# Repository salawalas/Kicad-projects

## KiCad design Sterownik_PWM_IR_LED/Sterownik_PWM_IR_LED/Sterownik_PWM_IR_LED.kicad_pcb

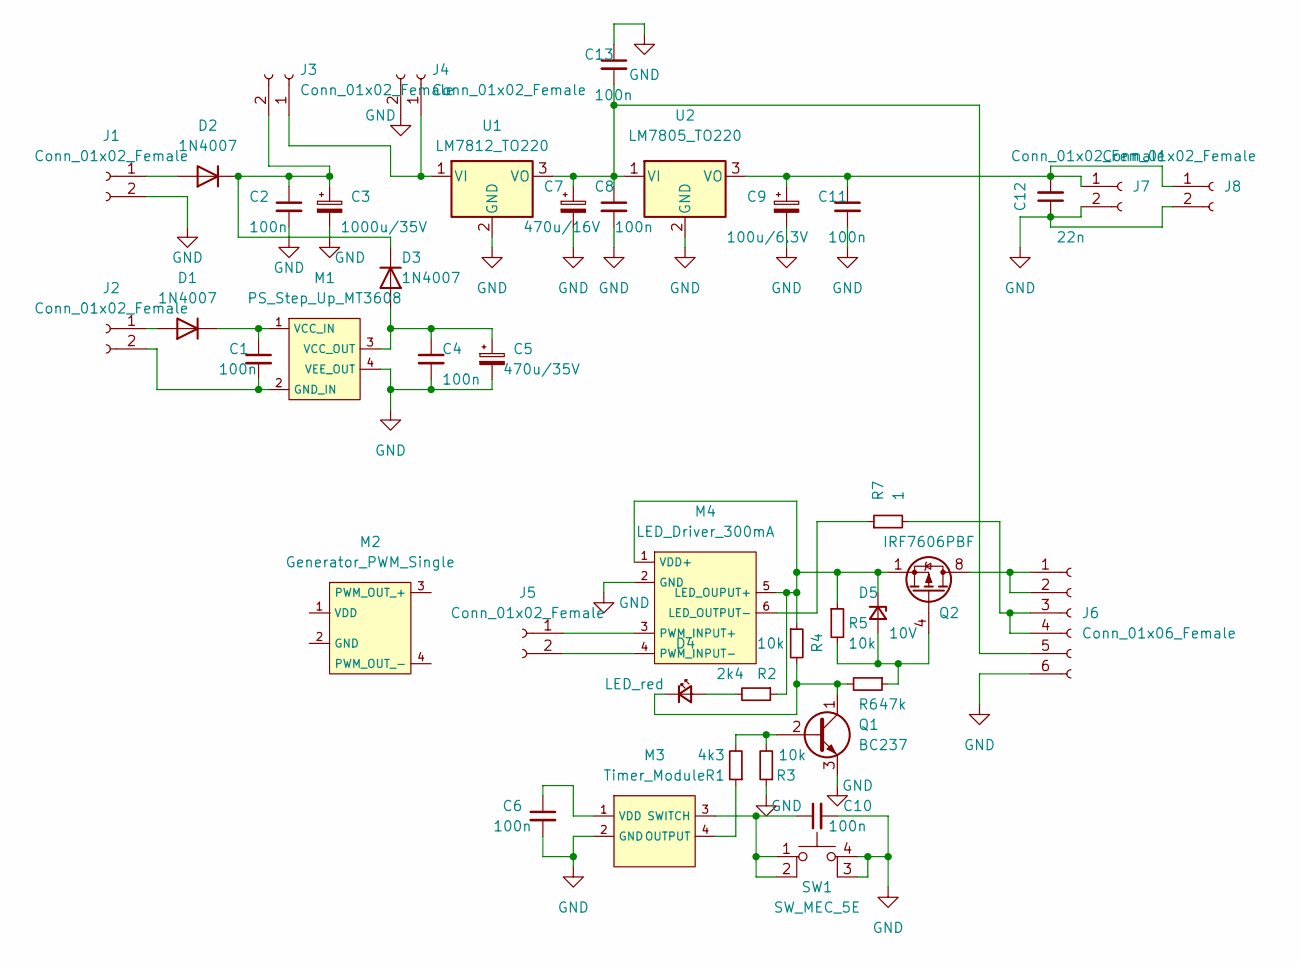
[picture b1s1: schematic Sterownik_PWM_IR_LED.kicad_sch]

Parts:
C1, C2, C4, C8, C11: 100n; C_Rect_L10.0mm_W2.5mm_P7.50mm_MKS4
C3: 1000u/35V; C_Radial_D10.0mm_H20.0mm_P5.00mm
C5: 470u/35V; C_Radial_D10.0mm_H16.0mm_P5.00mm
C6, C10, C13: 100n; C_Disc_D4.7mm_W2.5mm_P5.00mm
C7: 470u/16V; C_Radial_D8.0mm_H11.5mm_P3.50mm
C9: 100u/6.3V; C_Radial_D6.3mm_H7.0mm_P2.50mm
C12: 22n; C_Disc_D4.7mm_W2.5mm_P5.00mm
D1, D2, D3: 1N4007; D_DO-41_SOD81_P10.16mm_Horizontal
D4: LED_red; LED_D3.0mm
D5: 10V; D_DO-34_SOD68_P10.16mm_Horizontal
J1, J2, J3, J4: Conn_01x02_Female; Molex_KK-254_AE-6410-02A_1x02_P2.54mm_Vertical
J5, J7, J8: Conn_01x02_Female; JST_PH_B2B-PH-K_1x02_P2.00mm_Vertical
J6: Conn_01x06_Female; Molex_KK-254_AE-6410-06A_1x06_P2.54mm_Vertical
M1: PS_Step_Up_MT3608; PS_StepUp_MT3608
M2: Generator_PWM_Single
M3: Timer_Module; Timer
M4: LED_Driver_300mA
Q1: BC237; TO-92_Inline
Q2: IRF7606PBF; SO-8_3.9x4.9mm_P1.27mm
R1: 4k3; R_Axial_DIN0207_L6.3mm_D2.5mm_P10.16mm_Horizontal
R2: 2k4; R_Axial_DIN0207_L6.3mm_D2.5mm_P10.16mm_Horizontal
R3, R4, R5: 10k; R_Axial_DIN0207_L6.3mm_D2.5mm_P10.16mm_Horizontal
R6: 47k; R_Axial_DIN0207_L6.3mm_D2.5mm_P10.16mm_Horizontal
R7: 1; R_Axial_DIN0411_L9.9mm_D3.6mm_P12.70mm_Horizontal
SW1: SW_MEC_5E; Tact_switch 6x6
U1: LM7812_TO220; TO-220-3_Horizontal_TabDown
U2: LM7805_TO220; TO-220-3_Vertical

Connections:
unnamed: C1.1, D1.1 (K), M1.1 (VCC_IN)
unnamed: C1.2, J2.2, M1.2 (GND_IN)
unnamed: C4.1, C5.1, D3.2 (A), M1.3 (VCC_OUT)
unnamed: C6.1, M3.1 (VDD)
unnamed: C7.1, C8.1, C13.2, J6.5, U1.3 (VO), U2.1 (VI)
unnamed: C10.1, M3.3 (SWITCH), SW1.1, SW1.2
unnamed: C9.1, C11.1, C12.2, J7.1, J8.1, U2.3 (VO)
unnamed: D1.2 (A), J2.1
unnamed: D2.2 (A), J1.1
unnamed: D4.1 (K), Q1.1 (C), R4.2, R6.2
unnamed: D4.2 (A), R2.2
unnamed: D5.1 (K), M4.1 (VDD+), M4.5 (LED_OUPUT+), Q2.1 (S), Q2.2 (S), Q2.3 (S), R2.1, R4.1, R5.1
unnamed: D5.2 (A), Q2.4 (G), R5.2, R6.1
unnamed: J3.1, J4.1, U1.1 (VI)
unnamed: J5.1, M4.3 (PWM_INPUT+)
unnamed: J5.2, M4.4 (PWM_INPUT-)
unnamed: J6.1, J6.2, Q2.5 (D), Q2.6 (D), Q2.7 (D), Q2.8 (D)
unnamed: J6.3, J6.4, R7.2
unnamed: M3.4 (OUTPUT), R1.1
unnamed: M4.6 (LED_OUTPUT-), R7.1
unnamed: Q1.2 (B), R1.2, R3.2

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
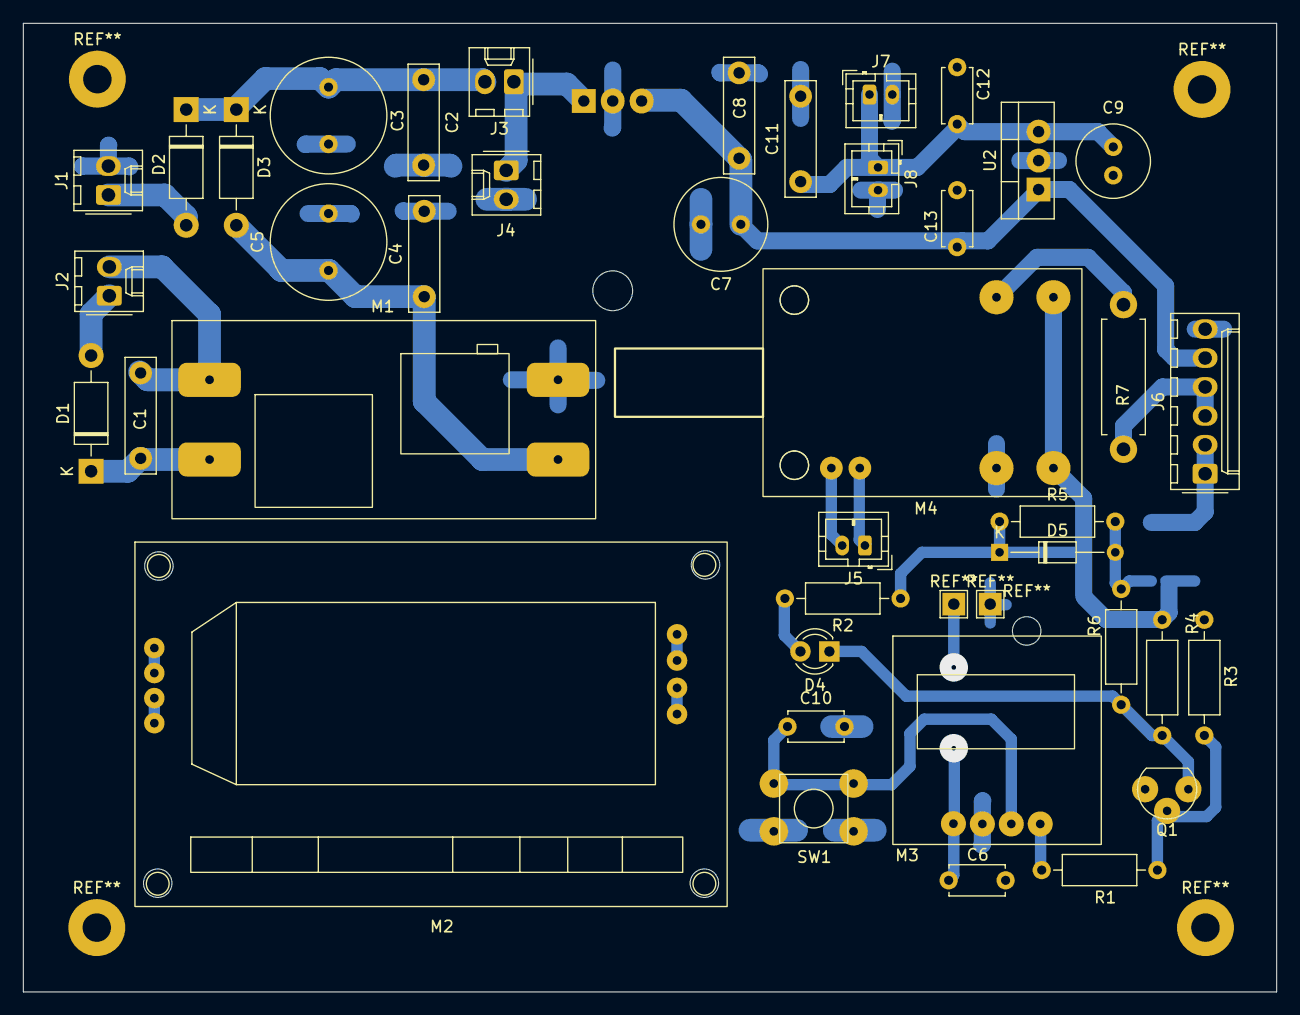
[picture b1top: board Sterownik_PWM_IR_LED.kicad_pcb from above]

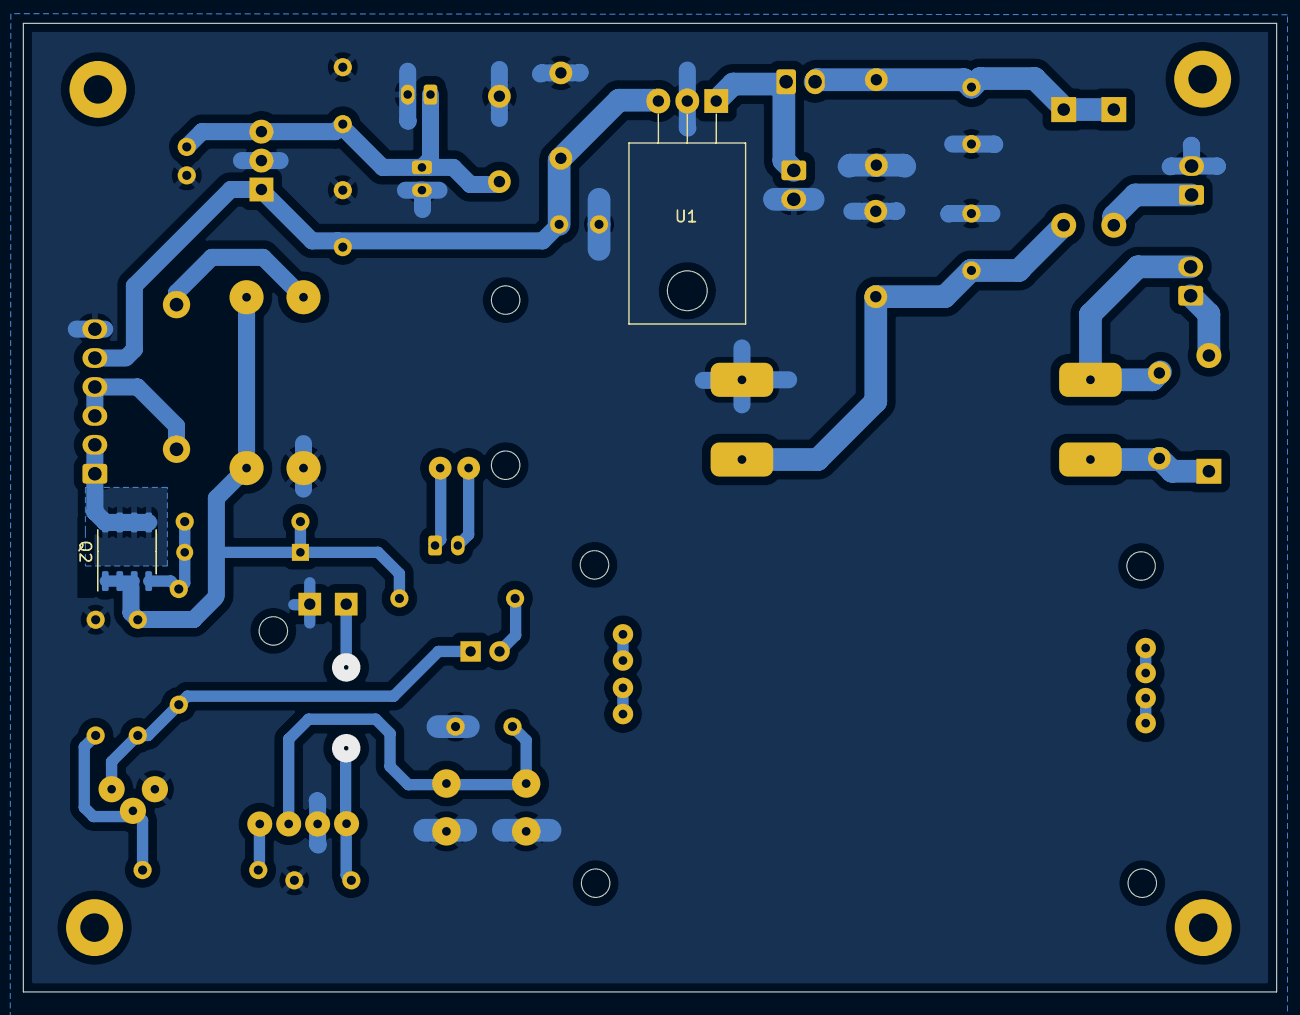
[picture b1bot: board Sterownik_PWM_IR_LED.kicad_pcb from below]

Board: 2 copper layers, 110.0 x 85.1 mm, 42 parts (2 on the bottom side), 23 nets.

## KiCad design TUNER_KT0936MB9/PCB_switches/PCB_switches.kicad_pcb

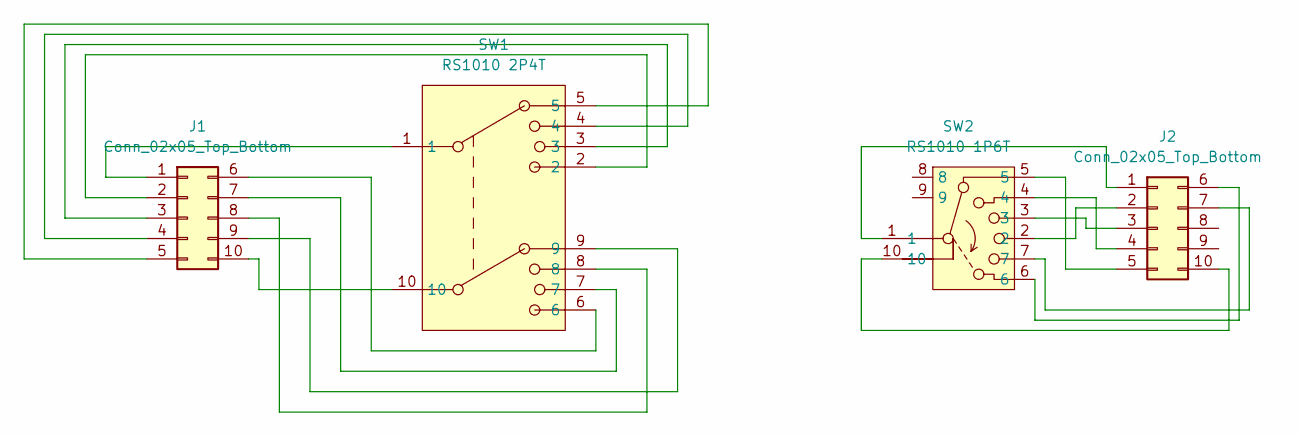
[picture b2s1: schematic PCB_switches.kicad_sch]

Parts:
J1, J2: Conn_02x05_Top_Bottom; JST_PHD_B10B-PHDSS_2x05_P2.00mm_Vertical
SW1: RS1010 2P4T
SW2: RS1010 1P6T

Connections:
unnamed: J1.1, SW1.1
unnamed: J1.2, SW1.2
unnamed: J1.3, SW1.3
unnamed: J1.4, SW1.4
unnamed: J1.5, SW1.5
unnamed: J1.6, SW1.6
unnamed: J1.7, SW1.7
unnamed: J1.8, SW1.8
unnamed: J1.9, SW1.9
unnamed: J1.10, SW1.10
unnamed: J2.1, SW2.1
unnamed: J2.2, SW2.2
unnamed: J2.3, SW2.3
unnamed: J2.4, SW2.4
unnamed: J2.5, SW2.5
unnamed: J2.6, SW2.6
unnamed: J2.7, SW2.7
unnamed: J2.10, SW2.10

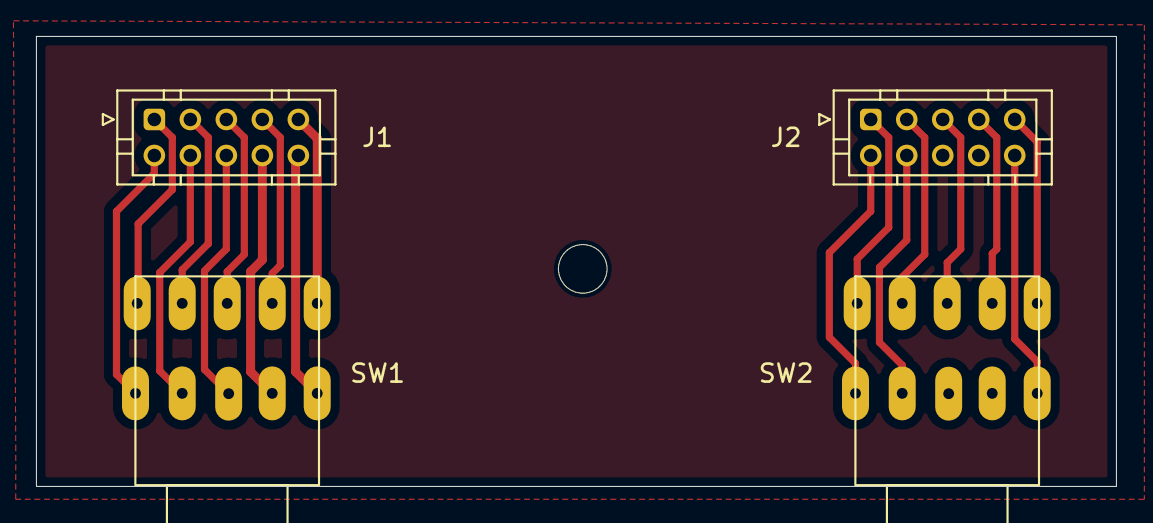
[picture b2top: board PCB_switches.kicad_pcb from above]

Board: 2 copper layers, 60.0 x 25.0 mm, 4 parts (0 on the bottom side), 18 nets.

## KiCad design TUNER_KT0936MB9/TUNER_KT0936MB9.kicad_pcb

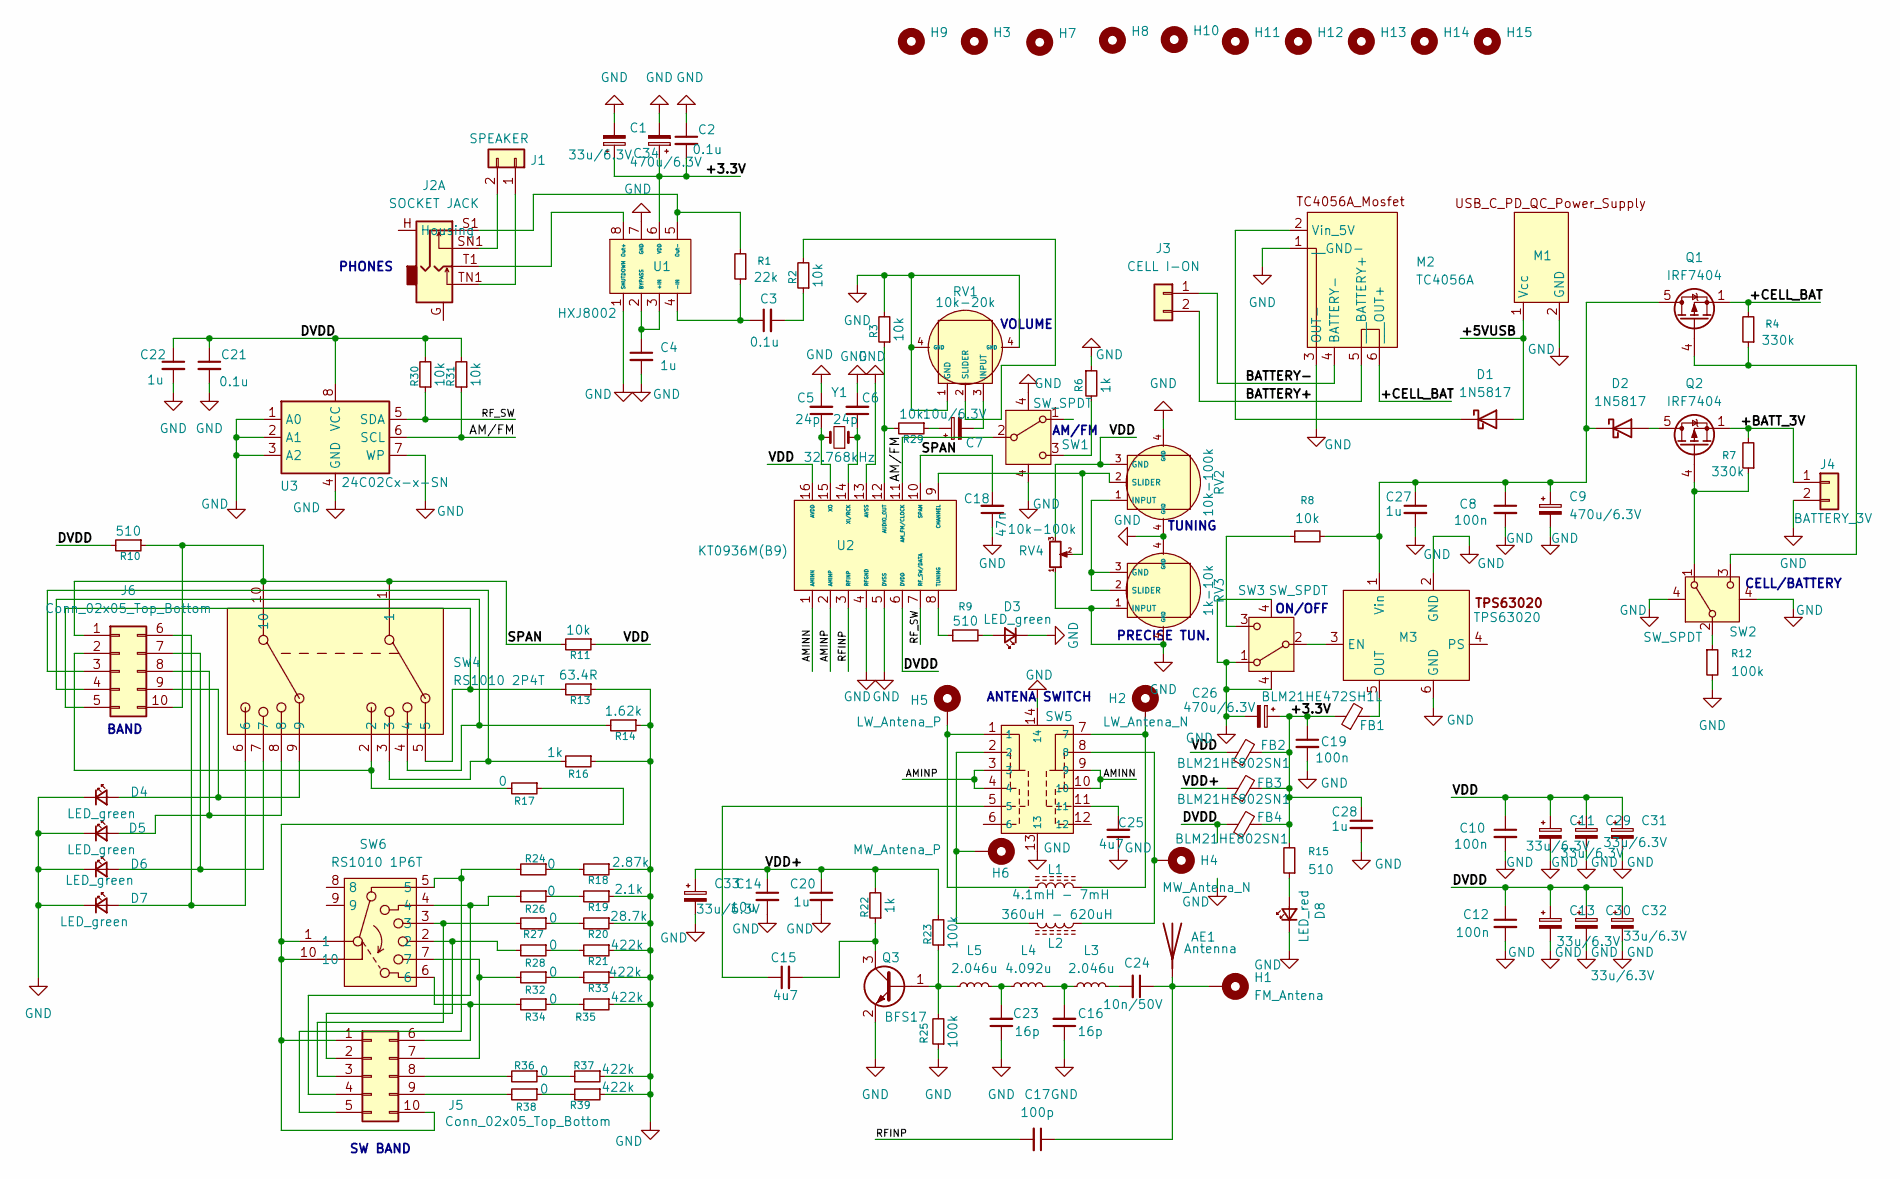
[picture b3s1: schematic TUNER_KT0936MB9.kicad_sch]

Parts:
AE1: Antenna
C1: 470u/6.3V; CP_Radial_D8.0mm_P3.80mm
C2, C3, C21: 0.1u; C_1206_3216Metric
C4, C20, C22, C27, C28: 1u; C_1206_3216Metric
C5, C6: 24p; C_0805_2012Metric
C7: 10u/6.3V; CP_Radial_D5.0mm_P2.50mm
C8, C10, C12, C19: 100n; C_1206_3216Metric
C9, C26: 470u/6.3V; CP_Radial_D8.0mm_P3.50mm
C11, C13, C29, C30, C31, C32, C33, C34: 33u/6.3V; CP_Radial_Tantal_D4.5mm_P2.50mm
C14: 10u; C_1206_3216Metric
C15, C25: 4u7; C_1206_3216Metric
C16, C23: 16p; C_0805_2012Metric
C17: 100p; C_0805_2012Metric
C18: 47n; C_0805_2012Metric
C24: 10n/50V; C_0805_2012Metric
D1, D2: 1N5817; D_DO-41_SOD81_P10.16mm_Horizontal
D3, D4, D5, D6, D7: LED_green; LED_D3.0mm
D8: LED_red; LED_D3.0mm
FB1: BLM21HE472SH1L; L_0805_2012Metric
FB2, FB3, FB4: BLM21HE802SN1; L_0805_2012Metric
H1: FM_Antena; SolderWire-0.1sqmm_1x01_D0.4mm_OD1mm
H2: LW_Antena_N; SolderWire-0.1sqmm_1x01_D0.4mm_OD1mm
H3, H7, H8, H9, H10, H11, H12, H13, H14, H15: MountingHole; MountingHole_2.2mm_M2
H4: MW_Antena_N; SolderWire-0.1sqmm_1x01_D0.4mm_OD1mm
H5: LW_Antena_P; SolderWire-0.1sqmm_1x01_D0.4mm_OD1mm
H6: MW_Antena_P; SolderWire-0.1sqmm_1x01_D0.4mm_OD1mm
J1: SPEAKER; JST_EH_B2B-EH-A_1x02_P2.50mm_Vertical
J2: SOCKET JACK; Jack_3.5mm_PJ31060-I_Horizontal
J3: CELL I-ON; JST_EH_B2B-EH-A_1x02_P2.50mm_Vertical
J4: BATTERY_3V; JST_EH_B2B-EH-A_1x02_P2.50mm_Vertical
J5, J6: Conn_02x05_Top_Bottom; JST_PHD_B10B-PHDSS_2x05_P2.00mm_Vertical
L1: 4.1mH - 7mH
L2: 360uH - 620uH
L3, L5: 2.046u; Cewka_5mm_LITZA
L4: 4.092u; Cewka_5mm_LITZA
M1: USB_C_PD_QC_Power_SupplyUSB_C_PS
M2: TC4056A; TC4056A_Mosfet
M3: TPS63020; TPS63020_module
Q1, Q2: IRF7404; SOIC-8_3.9x4.9mm_P1.27mm
Q3: BFS17; SOT-23
R1: 22k; R_1206_3216Metric
R2, R3, R11, R29, R30, R31: 10k; R_0805_2012Metric
R4, R7: 330k; R_1206_3216Metric
R6, R22: 1k; R_0805_2012Metric
R8: 10k; R_1206_3216Metric
R9, R10, R15: 510; R_1206_3216Metric
R12: 100k; R_1206_3216Metric
R13: 63.4R; R_1206_3216Metric
R14: 1.62k; R_1206_3216Metric
R16: 1k; R_1206_3216Metric
R17, R24, R26, R27, R28, R32, R34, R36, R38: 0; R_1206_3216Metric
R18: 2.87k; R_1206_3216Metric
R19: 2.1k; R_1206_3216Metric
R20: 28.7k; R_1206_3216Metric
R21, R33, R35, R37, R39: 422k; R_1206_3216Metric
R23, R25: 100k; R_0805_2012Metric
RV1: 10k-20k; Potencjometr_pojedynczy_thumbweel.mp3
RV2: 10k-100k; Potencjometr_pojedynczy_thumbweel.mp3
RV3: 1k-10k; Potencjometr_pojedynczy_thumbweel.mp3
RV4: 10k-100k; Potentiometer_Bourns_3296W_Vertical
SW1: SW_SPDT; SS-12F44G5
SW2, SW3: SW_SPDT; SK-12D07VG5
SW4: RS1010 2P4T
SW5: SK-24D02-G4
SW6: RS1010 1P6T
U1: HXJ8002; SOP-8_3.76x4.96mm_P1.27mm
U2: KT0936M(B9); SOP-16_3.9x9.9mm_P1.27mm
U3: 24C02Cx-x-SN; SOIC-8_3.9x4.9mm_P1.27mm
Y1: 32.768kHz; Crystal_AT310_D3.0mm_L10.0mm_Horizontal

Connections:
/+3.3V: C1.1, C2.2, C19.1, C26.1, C28.1, C34.1, FB1.1, FB2.2, FB3.2, FB4.2, R15.2, U1.6 (VDD)
/+5VUSB: D1.2 (A), M1.1 (Vcc)
/+BATT_3V: J4.1, Q2.1 (S), Q2.2 (S), Q2.3 (S), R7.2
/+CELL_BAT: M2.6 (___OUT+), Q1.1 (S), Q1.2 (S), Q1.3 (S), R4.2
/AMINN: SW5.9, SW5.10, U2.1 (AMINN)
/AMINP: SW5.3, SW5.4, U2.2 (AMINP)
/AM/FM: R31.1, SW1.2 (B), U2.11 (AM_FM/CLOCK), U3.6 (SCL)
/BATTERY+: J3.2, M2.5 (___BATTERY+)
/BATTERY-: J3.1, M2.4 (BATTERY-)
/DVDD: C12.1, C13.1, C21.1, C22.1, C30.1, C32.1, FB4.1, R10.2, R30.2, R31.2, U2.6 (DVDD), U3.8 (VCC)
/RFINP: C17.2, U2.3 (RFINP)
/RF_SW: R30.1, U2.7 (RF_SW/DATA), U3.5 (SDA)
/SPAN: C18.2, J6.1, J6.10, R10.1, R11.2, SW4.1, SW4.10, U2.10 (SPAN)
/VDD: C10.1, C11.1, C29.1, C31.1, FB2.1, R11.1, RV2.3 (GND), RV4.3, U2.16 (AVDD)
/VDD+: C14.1, C20.1, C33.1, FB3.1, R22.2, R23.2
GND: C1.2, C2.1, C4.2, C5.2, C6.2, C8.2, C9.2, C10.2, C11.2, C12.2, C13.2, C14.2, C16.1, C18.1, C19.2, C20.2, C21.2, C22.2, C23.1, C25.1, C26.2, C27.2, C28.2, C29.2, C30.2, C31.2, C32.2, C33.2, C34.2, D3.1 (K), D4.1 (K), D5.1 (K), D6.1 (K), D7.1 (K), D8.1 (K), J4.2, M1.2 (GND), M2.1 (__GND-), M2.3 (OUT-), M3.2 (GND), M3.6 (GND), Q3.2 (E), R3.2, R6.1, R12.2, R13.1, R14.1, R16.1, R18.1, R19.1, R20.1, R21.1, R25.1, R33.1, R35.1, R37.1, R39.1, RV1.1 (GND), RV1.4 (GND), RV2.4 (GND), RV3.1 (INPUT), RV3.4 (GND), RV4.1, SW1.4, SW2.4, SW3.1 (A), SW3.4, SW5.13, SW5.14, U1.1 (SHUTDOWN), U1.7 (GND), U2.4 (RFGND), U2.5 (DVSS), U2.13 (AVSS), U3.1 (A0), U3.2 (A1), U3.3 (A2), U3.4 (GND), U3.7 (WP)
unnamed: C3.2, R2.1
unnamed: C7.1, R29.1
unnamed: C15.1, SW5.5
unnamed: C16.2, L3.1, L4.2
unnamed: AE1.1, C17.1, C24.1, H1.1
unnamed: C23.2, L4.1, L5.2
unnamed: C24.2, L3.2
unnamed: C25.2, SW5.11
unnamed: D1.1 (K), M2.2 (Vin_5V)
unnamed: D2.2 (A), Q2.5 (D), Q2.6 (D), Q2.7 (D), Q2.8 (D)
unnamed: C8.1, C9.1, C27.1, D2.1 (K), M3.1 (Vin), Q1.5 (D), Q1.6 (D), Q1.7 (D), Q1.8 (D), R8.2
unnamed: D3.2 (A), R9.2
unnamed: D4.2 (A), J6.9, SW4.9
unnamed: D5.2 (A), J6.8, SW4.8
unnamed: D6.2 (A), J6.7, SW4.7
unnamed: D7.2 (A), J6.6, SW4.6
unnamed: D8.2 (A), R15.1
unnamed: H2.1, L1.2, SW5.7
unnamed: H4.1, L2.1, SW5.8
unnamed: H5.1, L1.1, SW5.1
unnamed: H6.1, L2.2, SW5.2
unnamed: J1.1, J2.TN1
unnamed: J1.2, J2.SN1
unnamed: J5.1, J5.10, R17.1, SW6.1, SW6.10
unnamed: J5.2, R28.2, SW6.2
unnamed: J5.3, R27.2, SW6.3
unnamed: J5.4, R26.2, SW6.4
unnamed: J5.5, R24.2, SW6.5
unnamed: J5.6, R34.2, SW6.6
unnamed: J5.7, R32.2, SW6.7
unnamed: J5.8, R36.2
unnamed: J5.9, R38.2
unnamed: J6.2, R17.2, SW4.2
unnamed: J6.3, R16.2, SW4.3
unnamed: J6.4, R14.2, SW4.4
unnamed: J6.5, R13.2, SW4.5
unnamed: M3.3 (EN), SW3.2 (B)
unnamed: FB1.2, M3.5 (OUT)
unnamed: Q1.4 (G), R4.1, SW2.3 (C)
unnamed: Q2.4 (G), R7.1, SW2.1 (A)
unnamed: L5.1, Q3.1 (B), R23.1, R25.2
unnamed: C15.2, Q3.3 (C), R22.1
unnamed: R18.2, R24.1
unnamed: R19.2, R26.1
unnamed: R20.2, R27.1
unnamed: R21.2, R28.1
unnamed: R32.1, R33.2
unnamed: R34.1, R35.2
unnamed: R36.1, R37.2
unnamed: R38.1, R39.2
unnamed: C7.2, RV1.3 (INPUT)
unnamed: R2.2, RV1.2 (SLIDER)
unnamed: RV2.1 (INPUT), RV3.2 (SLIDER), RV3.3 (GND)
unnamed: RV2.2 (SLIDER), RV4.2, U2.9 (CHANNEL)
unnamed: R6.2, SW1.3 (C)
unnamed: R12.1, SW2.2 (B)
unnamed: R8.1, SW3.3 (C)
unnamed: C4.1, U1.2 (BYPASS), U1.3 (+IN)
unnamed: C3.1, R1.1, U1.4 (-IN)
unnamed: J2.T1, U1.8 (Out+)
unnamed: J2.S1, R1.2, U1.5 (Out-)
unnamed: R3.1, R29.2, U2.12 (AUDIO_OUT)
unnamed: R9.1, U2.8 (TUNING)
unnamed: C6.1, U2.14 (XI/RCK), Y1.1
unnamed: C5.1, U2.15 (XO), Y1.2

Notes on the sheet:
ANTENA SWITCH
TUNING
PHONES
ON/OFF
VOLUME
AM/FM
CELL/BATTERY
BAND
PRECISE TUN.
SW BAND

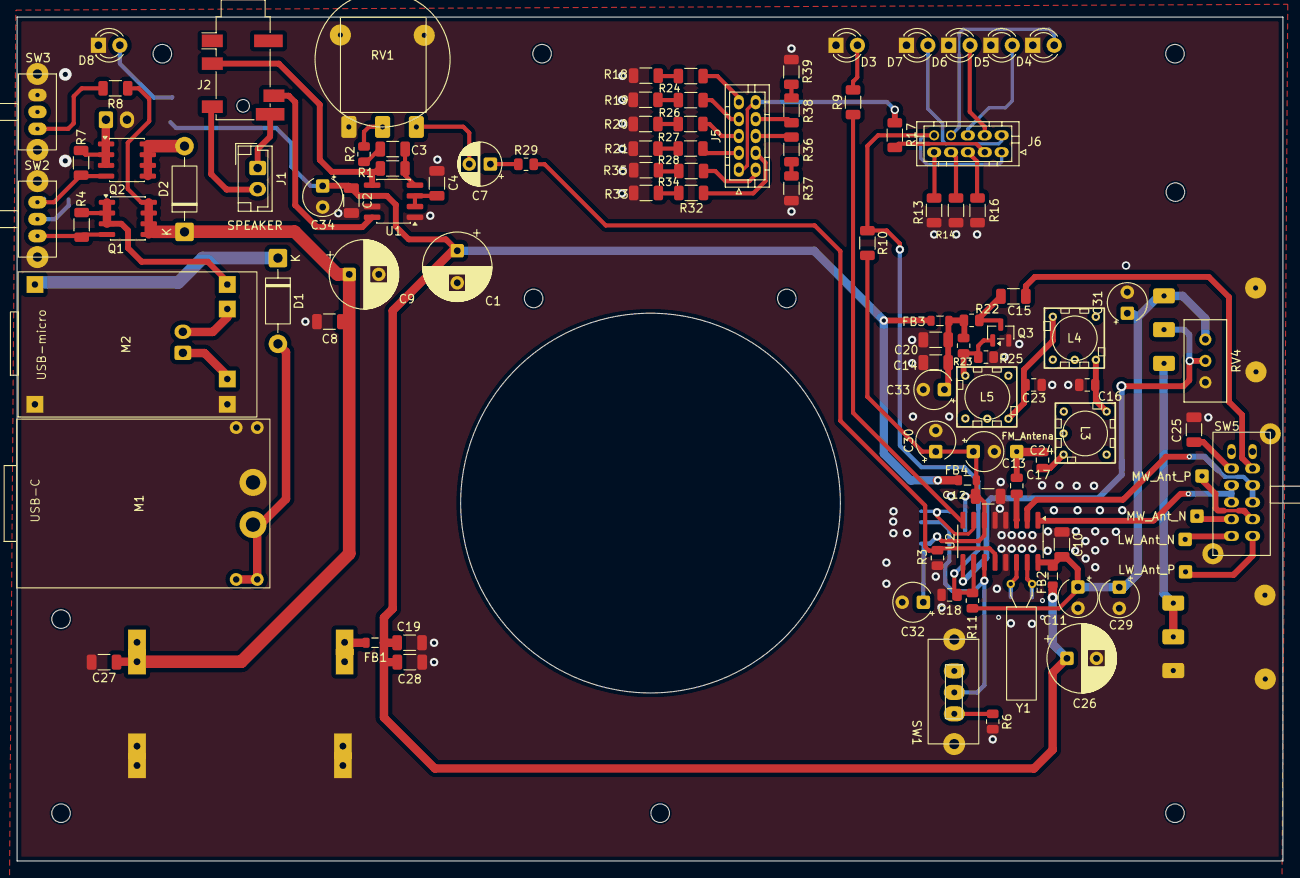
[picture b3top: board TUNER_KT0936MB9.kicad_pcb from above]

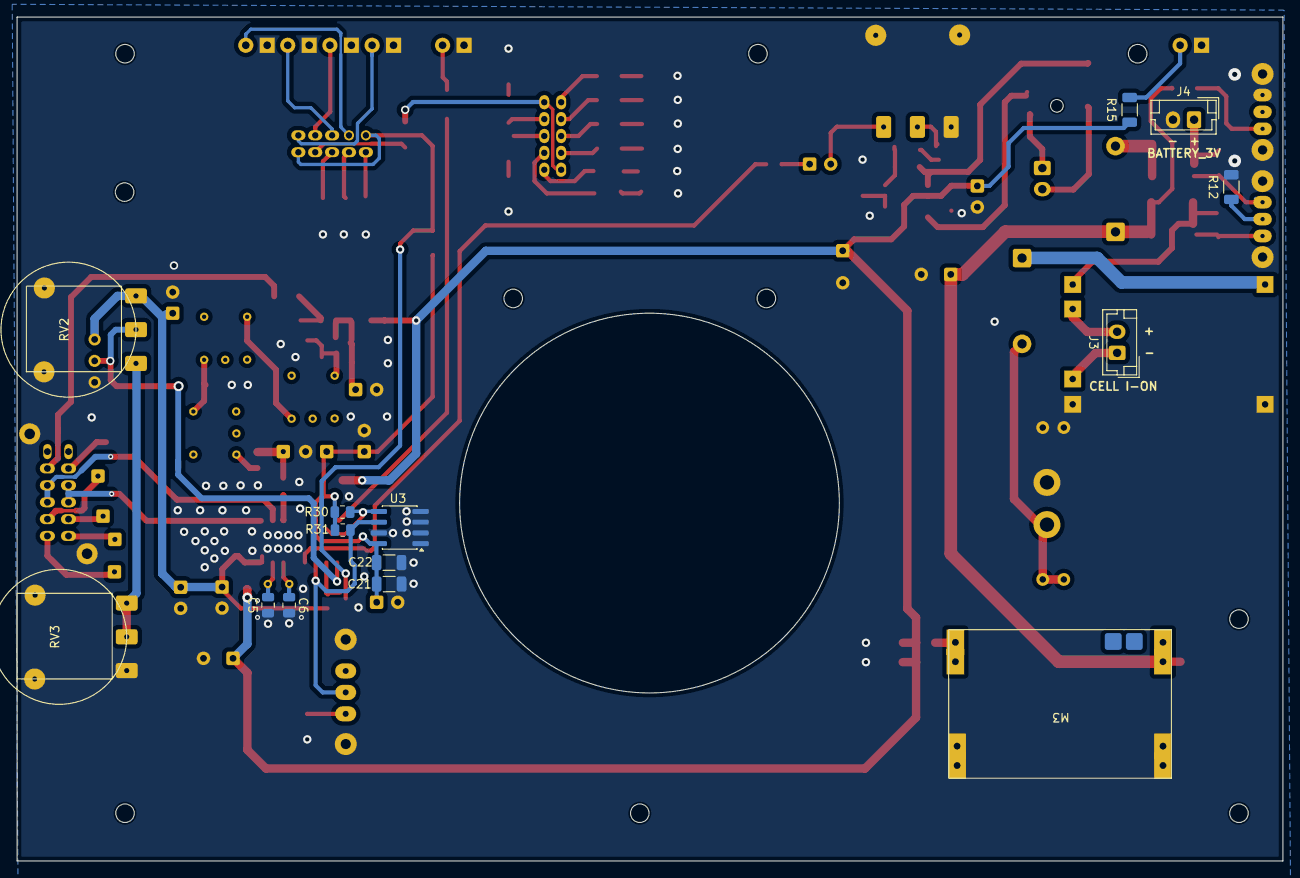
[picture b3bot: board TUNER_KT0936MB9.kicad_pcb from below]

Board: 2 copper layers, 150.0 x 100.0 mm, 126 parts (14 on the bottom side), 81 nets.

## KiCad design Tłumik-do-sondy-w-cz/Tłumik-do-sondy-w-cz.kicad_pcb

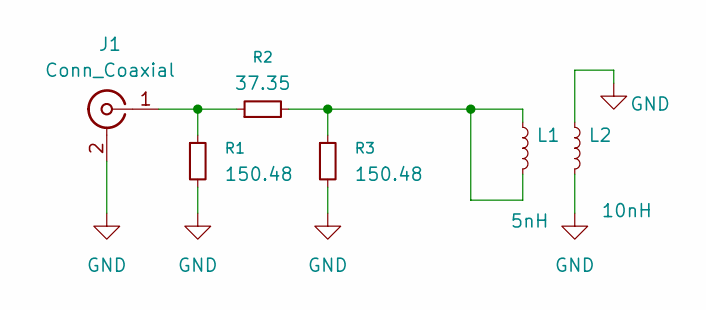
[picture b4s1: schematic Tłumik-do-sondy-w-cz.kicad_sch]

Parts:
J1: Conn_Coaxial; SMA_Molex_73251-1153_EdgeMount_Horizontal
L1: 5nH; L_Radial_D6.0mm_P4.00mm
L2: 10nH; L_Radial_D12.0mm_P10.00mm_Neosid_SD12k_style1
R1, R3: 150.48; R_0805_2012Metric
R2: 37.35; R_0805_2012Metric

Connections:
GND: J1.2 (Ext), L2.1, L2.2, R1.2, R3.2
unnamed: J1.1 (In), R1.1, R2.1
unnamed: L1.1, L1.2, R2.2, R3.1

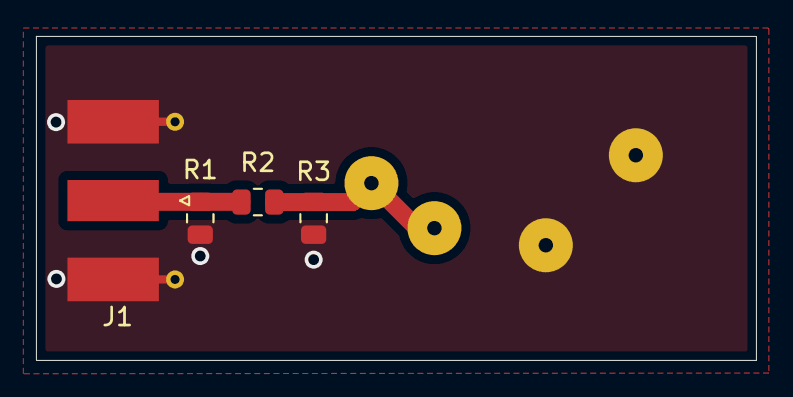
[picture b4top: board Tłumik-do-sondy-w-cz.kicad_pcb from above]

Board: 4 copper layers, 40.0 x 18.0 mm, 6 parts (0 on the bottom side), 3 nets.

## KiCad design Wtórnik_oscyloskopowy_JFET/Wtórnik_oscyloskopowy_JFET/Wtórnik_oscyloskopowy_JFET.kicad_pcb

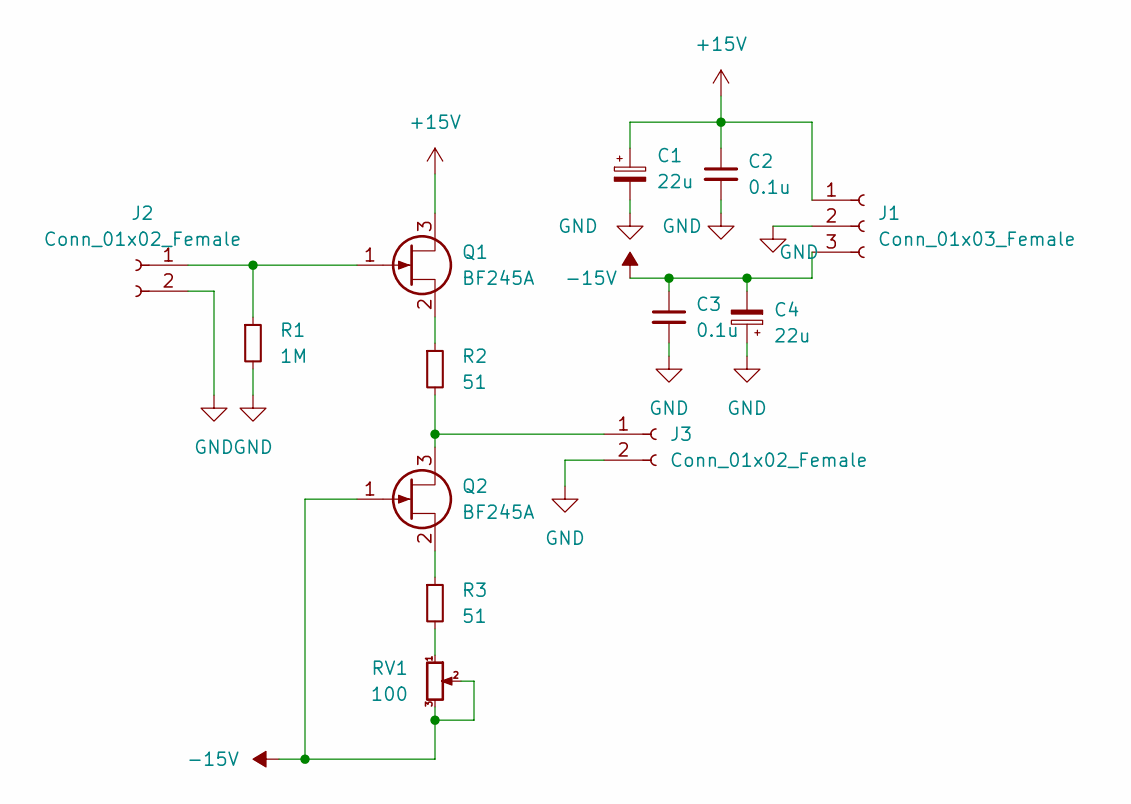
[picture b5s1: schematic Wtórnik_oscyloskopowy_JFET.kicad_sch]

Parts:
C1, C4: 22u; CP_Radial_Tantal_D5.0mm_P5.00mm
C2, C3: 0.1u; C_0805_2012Metric
J1: Conn_01x03_Female; PinHeader_1x03_P2.54mm_Vertical
J2, J3: Conn_01x02_Female; PinHeader_1x02_P2.54mm_Vertical
Q1, Q2: BF245A; TO-92
R1: 1M; R_0805_2012Metric
R2, R3: 51; R_0805_2012Metric
RV1: 100; Potentiometer_Bourns_3266Y_Vertical

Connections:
+15V: C1.1, C2.1, J1.1, Q1.3 (D)
-15V: C3.1, C4.2, J1.3, Q2.1 (G), RV1.2, RV1.3
GND: C1.2, C2.2, C3.2, C4.1, J1.2, J2.2, J3.2, R1.2
unnamed: J2.1, Q1.1 (G), R1.1
unnamed: J3.1, Q2.3 (D), R2.2
unnamed: Q1.2 (S), R2.1
unnamed: Q2.2 (S), R3.1
unnamed: R3.2, RV1.1

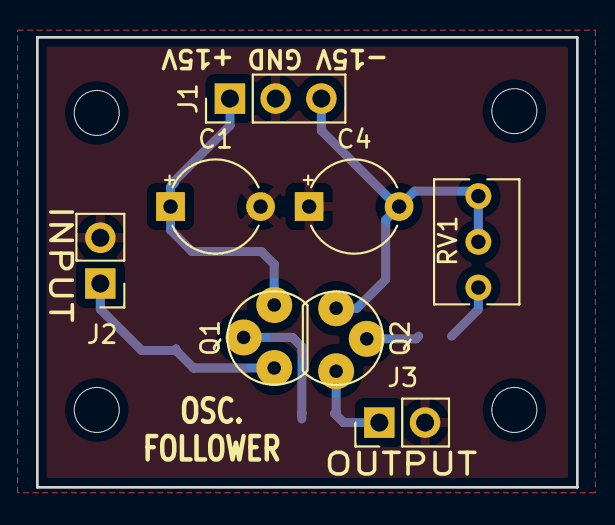
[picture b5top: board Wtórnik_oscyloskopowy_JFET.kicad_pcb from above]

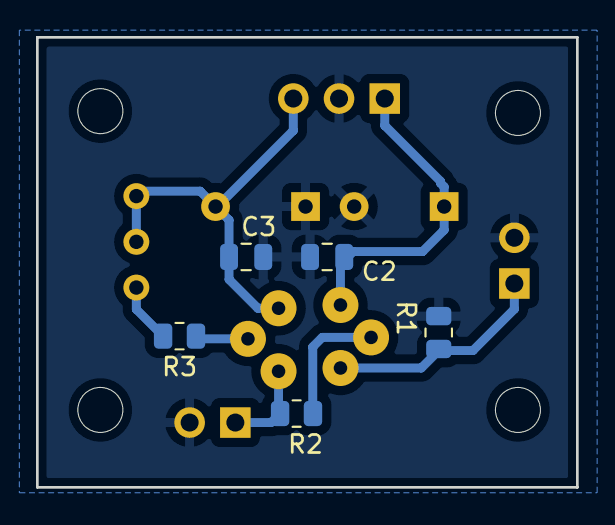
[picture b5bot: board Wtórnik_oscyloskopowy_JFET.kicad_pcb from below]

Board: 2 copper layers, 30.0 x 25.0 mm, 13 parts (5 on the bottom side), 8 nets.

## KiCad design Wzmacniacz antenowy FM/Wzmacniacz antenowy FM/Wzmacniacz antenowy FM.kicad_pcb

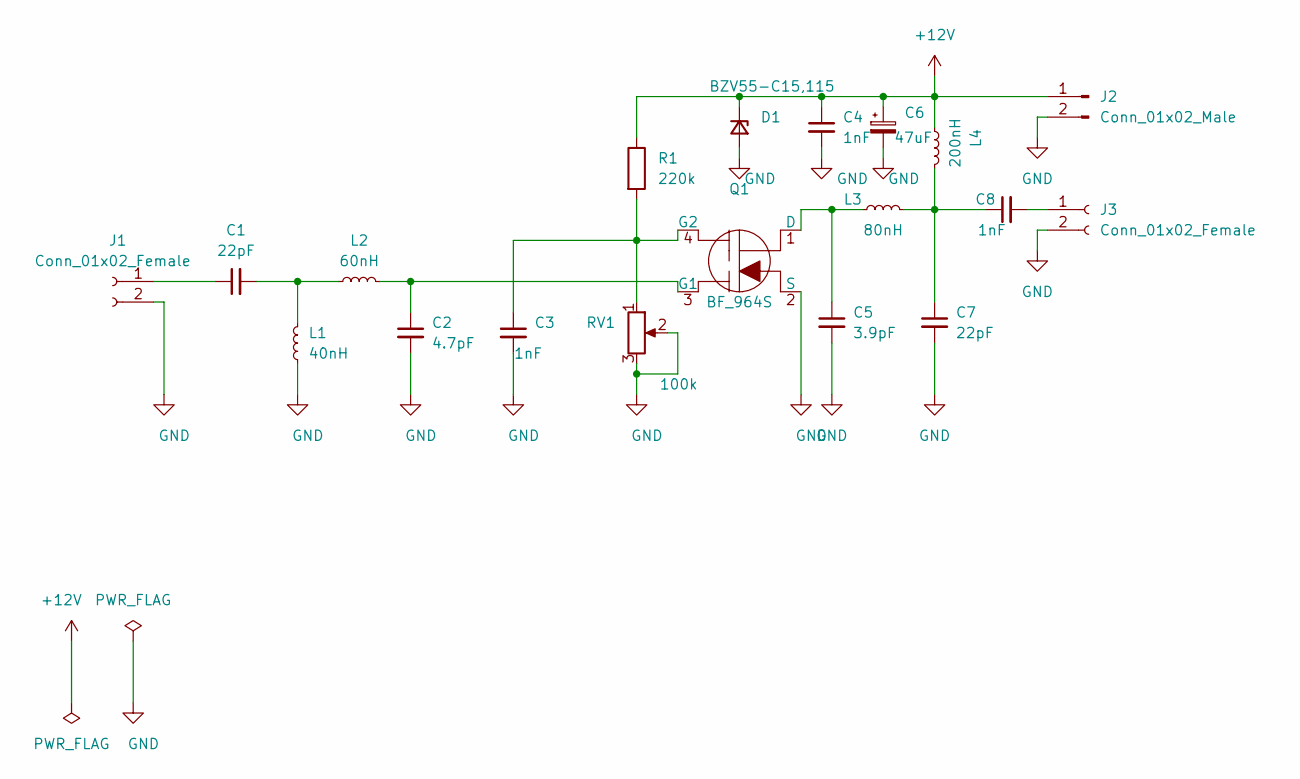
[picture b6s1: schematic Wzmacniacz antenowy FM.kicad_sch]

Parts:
C1, C7: 22pF; C_0805_2012Metric
C2: 4.7pF; C_0805_2012Metric
C3, C4, C8: 1nF; C_0805_2012Metric
C5: 3.9pF; C_0805_2012Metric
C6: 47uF; CP_Elec_6.3x5.9
D1: BZV55-C15,115; D_MiniMELF
J1, J3: Conn_01x02_Female; SMA_Amphenol_132203-12_Horizontal
J2: Conn_01x02_Male; JST_PH_B2B-PH-K_1x02_P2.00mm_Vertical
L1: 40nH; inductor_horizontal_6mm_5.5
L2: 60nH; inductor_horizontal_6mm_6.4mm
L3: 80nH; inductor_horizontal_6mm_8mm
L4: 200nH; inductor_horizontal_4mm_11mm
Q1: BF_964S; TO-50_Long_Pad_SMT
R1: 220k; R_0805_2012Metric
RV1: 100k; Potentiometer_Bourns_3314J_Vertical

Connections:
+12V: C4.1, C6.1, D1.1 (K), J2.1, L4.1, R1.1
GND: C2.2, C3.2, C4.2, C5.2, C6.2, C7.2, D1.2 (A), J1.2, J2.2, J3.2, L1.1, Q1.2 (S), RV1.2, RV1.3
unnamed: C1.1, J1.1
unnamed: C1.2, L1.2, L2.1
unnamed: C2.1, L2.2, Q1.3 (G1)
unnamed: C3.1, Q1.4 (G2), R1.2, RV1.1
unnamed: C5.1, L3.1, Q1.1 (D)
unnamed: C7.1, C8.1, L3.2, L4.2
unnamed: C8.2, J3.1

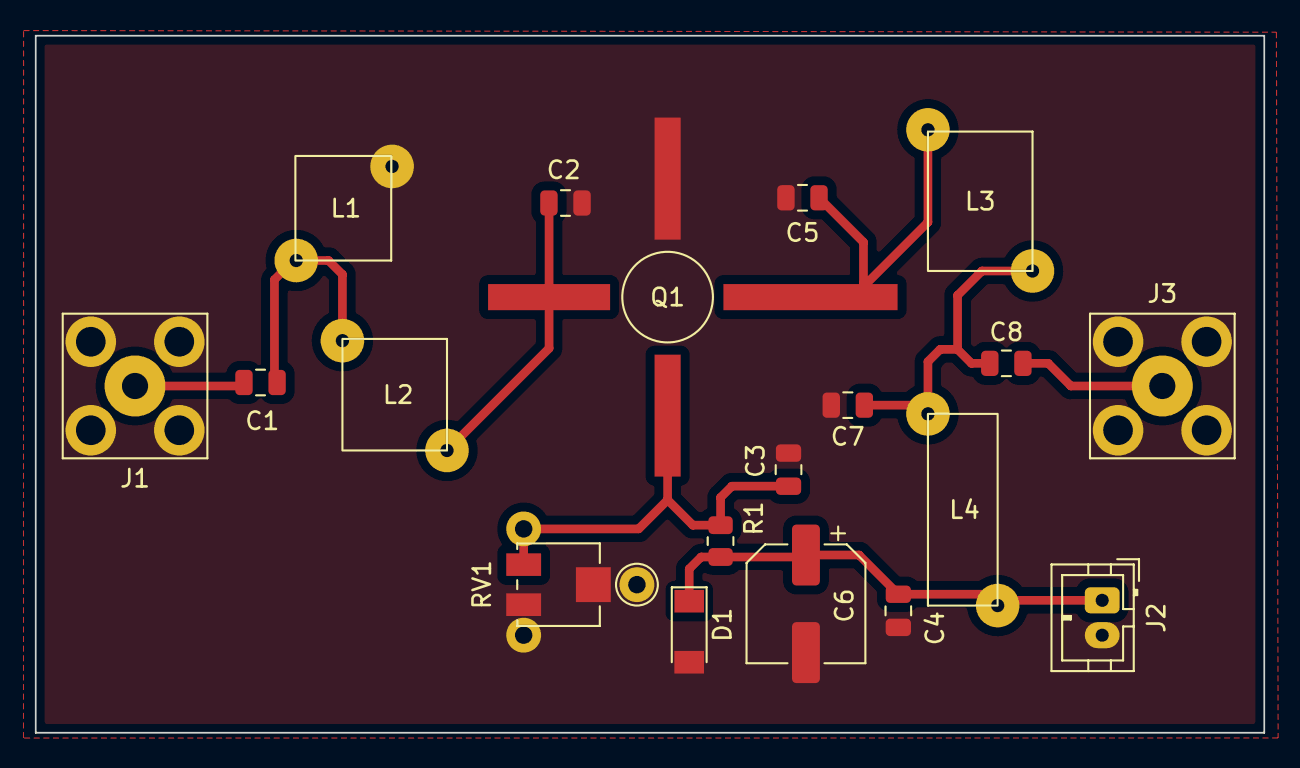
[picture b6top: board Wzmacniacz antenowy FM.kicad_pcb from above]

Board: 2 copper layers, 70.5 x 40.0 mm, 19 parts (0 on the bottom side), 9 nets.
